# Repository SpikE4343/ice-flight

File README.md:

# ice-flight
TinyFPGA-BX based quadcopter flight controller

# Test
```
cd src
apio sim
```

# Build
```
cd src
apio build
```

# TODO:
  - [x] 32bit memory for storing the fixed point flight data values
    * Split memories, one for each module (imu_mem, attitud_mem, motor_mem)?
    * Virtual mapping to combine all module memories into single memory? (mem map io?)
  - [ ] Define addresses for each flight variable
  - [ ] Move to memory storage for all values to reduce register count
  - [ ] Iterate main flight memory to send as a dump for debugging

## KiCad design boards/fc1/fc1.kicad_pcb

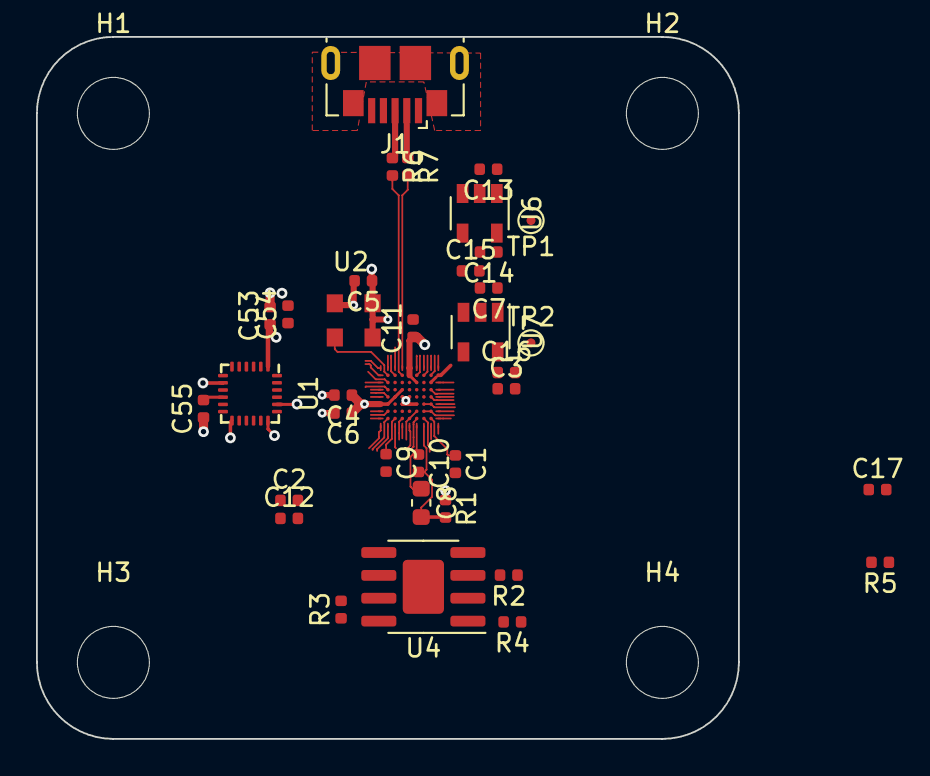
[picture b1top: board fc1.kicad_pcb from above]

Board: 4 copper layers, 39.0 x 39.0 mm, 40 parts (0 on the bottom side), 20 nets.

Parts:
C1, C2, C3, C5, C10, C11, C12: 100nF; C_0402_1005Metric
C4, C6, C7, C9, C53: 10nF; C_0402_1005Metric
C8: 10nF; C_0603_1608Metric
C13, C14, C15, C16: 1uF; C_0402_1005Metric
C17: 10uF; C_0402_1005Metric
C54, C55: 0.1uF; C_0402_1005Metric
H1, H2, H3, H4: MountingHole; MountingHole_4mm
J1: USB_OTG; USB_Micro-B_GCT_USB3076-30-A
R1: 100; R_0402_1005Metric
R2, R3, R4: 10k; R_0402_1005Metric
R5: 1.5k; R_0402_1005Metric
R6, R7: 68; R_0402_1005Metric
TP1, TP2: TestPoint; TestPoint_Pad_D1.0mm
U1: MPU-9250; InvenSense_QFN-24_3x3mm_P0.4mm
U2: DSC6001CI2A-016.0000T; CDFN3225-4LD-PL-1
U3: iCE40-LP8K-CM81; CM81
U4: AT25SF041-SSHD-B; SOIC-8-1EP_3.9x4.9mm_P1.27mm_EP2.29x3mm
U6: MIC5504-3.3YM5; SOT-23-5
U7: MIC5504-1.2YM5; SOT-23-5

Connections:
+1V2: C3.1, C4.1, C6.1, C16.1, R1.1, TP2.1, U3.D4, U3.E3, U3.E9, U3.F1, U3.F2, U7.5
+3V3: C1.1, C2.1, C5.1, C7.1, C9.1, C11.1, C12.1, C14.1, C53.1, C54.1, R2.1, R3.1, R4.1, TP1.1, U1.1, U1.8, U1.13, U2.1, U2.4, U3.A5, U3.B5, U3.B9, U3.C6, U3.C8, U3.H3, U3.H8, U3.J5, U4.8, U6.5, U7.1
+5V: C13.1, U6.1, U6.3
CLK: U2.3, U3.B2
FLASH_CS: R4.2, U3.F7, U3.F8, U4.1
FLASH_MISO: U3.H7, U4.2
FLASH_MOSI: U3.G6, U3.H5, U4.5
FLASH_SCLK: U3.G7, U3.G8, U4.6
GND: C1.2, C2.2, C3.2, C4.2, C5.2, C6.2, C7.2, C9.2, C11.2, C12.2, C13.2, C14.2, C15.2, C16.2, C17.1, C53.2, C54.2, C55.1, J1.5, J1.6, U1.18, U1.20, U2.2, U3.E4, U3.E5, U3.F4, U3.F5, U3.F6, U3.F9, U4.4, U6.2, U7.2
unnamed: C8.1, C10.1, U3.J6
unnamed: C8.2, C10.2, R1.2, U3.J7
unnamed: C15.1, U7.3
unnamed: C55.2, U1.10
unnamed: J1.2, R7.1
unnamed: J1.3, R5.1, R6.1
unnamed: R2.2, U4.3
unnamed: R3.2, U4.7
USB_N: R7.2, U3.A4
USB_P: R6.2, U3.B4
USB_PU: R5.2, U3.A3

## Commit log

2020-05-11 Initial import
2020-05-12 Add datasheets and other information to docs folder. Add debug output state machine to send multiple messages. Reduced debug uart buffer to keep in 8k logic size. Need to port to ram model. Add Vivad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
2020-05-17 Unbuffered uart tx to reduce register count Working debug telemetry stream with realtime graphing of data
2020-06-09 Add digilent cmod-a7 with vivado project
2020-06-18 Add gyro sample data to testbench. Break out mixing logic to modules - still has some timing issues Add all telemetry message support to script Clean up lots of timing and signed/unsigned when conver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
2020-06-19 Update TinyFPGA support
2020-10-21 latest work
2020-10-24 Add write+read of flight block memory
2020-10-24 More work to copy TinyFPGA schematic and layout
2020-11-08 nmigen intial implemention of spi, uart, dshot
2020-11-08 Add virtual environment requirements file
2020-11-08 Add simple shell script to setup nmigen python virtual environment in
2020-11-13 More FPort decode work
2021-03-20 Bump jinja2 from 2.11.2 to 2.11.3 in /src/nmigen
    Bumps [jinja2](https://github.com/pallets/jinja) from 2.11.2 to 2.11.3.
    - [Release notes](https://github.com/pallets/jinja/releases)
    - [Changelog](https://github.com/pallets/jinja/blob/master/CHANGES.rst)
    - [Commits](https://github.com/pallets/jinja/compare/2.11.2...2.11.3)
